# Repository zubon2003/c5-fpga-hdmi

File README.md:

# c5-fpga-hdmi

[日本語の README](README.ja.md)

> **Experimental — close range only.** This has only been seen working with
> the VTX a short distance (about 1 m, on a desk) from the receiver. Range,
> weak-signal behaviour, other VTXs and other channels have not been tested.
> Treat it as a proof of concept, not as a usable FPV receiver.

Analog 5.8 GHz FPV video (FM, NTSC) received by an ESP32-C5 running
[C5VRX](https://github.com/Twotoz/C5VRX), demodulated on a Sipeed
**Tang Primer 25K** FPGA and shown in colour on an HDMI monitor at
**1280×720p, 59.94 Hz** (CEA 720p frame timing; a 4:3 picture, 960×720 with
black pillars, or stretched to 16:9). An SDRAM field store lets the HDMI
output run on a fixed pixel clock, which HDZero goggles need; with genlock
on, the output follows the input with about 1 ms of latency and no SDRAM.

The C5VRX-5 firmware already puts the radio's raw 4-bit IQ samples
(MODEM_DIAG Q4/I4) on eight GPIO pins. The FPGA taps those pins in
parallel; the ESP32-C5 firmware keeps doing the gain control, AFC and
channel selection. Official releases up to v5.0.464 work unmodified;
later ones moved two IQ pins, and [firmware/](firmware/README.md) has a
patched v5.0.523 (see [C5VRX version](#c5vrx-version)).

## Origins

- **[fpvdec / 5G8atv-rf-hackrf-decoder](https://github.com/zubon2003/5G8atv-rf-hackrf-decoder)**
  — my HackRF One software receiver for analog FPV video, which this
  project grew out of. It is itself based on
  [famicom-rf-hackrf-decoder](https://github.com/GOROman/famicom-rf-hackrf-decoder)
  by GOROman. Its NTSC decoder and its C5VRX receive-chain emulation
  (`--c5`) were the reference for the processing here; the FPGA design
  itself is newly written HDL.
- **[C5VRX](https://github.com/Twotoz/C5VRX)** by Twotoz and the C5VRX
  contributors — the ESP32-C5 FPV receiver. This project uses its
  MODEM_DIAG IQ GPIO output (lane mapping and pin order, C5VRX-5
  `main/rf.c`), follows its "C5 RF front end plus external DSP logic"
  research (C5VRX-4 `RESEARCH.md`), its sync separator uses the line
  grid idea of the C5VRX-4 sync flywheel (`SYNC_FLYWHEEL.md`), and its
  FM demodulator extends the C5VRX-5 U85Q phase tracker and kp ladder.
  See [Credits](#credits).

## Hardware

| Part | Notes |
|---|---|
| Seeed XIAO ESP32-C5 | running C5VRX-5 (see below) |
| Sipeed Tang Primer 25K + Tang Primer 25K Dock | GW5A-LV25MG121 |
| Sipeed PMOD DVI (HDMI) module | on Dock PMOD **J5** (middle) |
| Sipeed Tang SDRAM module (32 MB, 16 bit) | on the Dock's 40-pin header **J3**; field store (`src/sdram_fb.v`), needed for genlock off (power-up, HDZero) |
| HDMI monitor or capture device | 720p input |
| 9 jumper wires (8 signals + GND), short | XIAO → Dock PMOD **J4** |
| Analog 5.8 GHz VTX (NTSC) | tested on F3 (5780 MHz) |
| Optional: USB-A plug (breakout) + 3 wires | XIAO D4/D5 → Dock USB-A host port **J13**, for the Dock buttons (band / channel) and the on-screen channel; needs the modified C5 firmware below |

### C5VRX version

Tested with the official **C5VRX-5 release `c5vrx5-v5.0.332`**
(commit `24da232`), unmodified, flashed from the
[C5VRX web flasher](https://twotoz.github.io/C5VRX/) / GitHub release.
The IQ GPIO mapping below is the one in that version (also identical in
v5.0.322). Later versions may change it; check `RF_IQ_GPIO_NUMS` in
C5VRX's `main/rf.h` (`s_iq_pins` in `main/rf.c` before v5.0.482). Set the
channel on the C5 as usual (BOOT button menu or USB console) and let its
startup calibration finish.

**Official releases from `c5vrx5-v5.0.482` on do not work with this
wiring.** C5VRX PR #263 moved Q sign from D3/GPIO7 to GPIO2 (MTMS) and
I bit 0 from D10/GPIO10 to the user-LED GPIO27, which is not on a pad.
Official releases up to `c5vrx5-v5.0.464` keep the old pins (only
v5.0.332 is tested unmodified here); the modified v5.0.523 in
[firmware/](firmware/README.md) puts both bits back.

### Optional: band / channel buttons on the Dock

To step the band and channel with the Dock's buttons and see the channel
on screen, the C5 needs a modified C5VRX-5 with a UART on its two DAC LSB
pins: [firmware/](firmware/README.md) has the patches (v5.0.523, tested
2026-10-27; the older v5.0.387 one) and the build steps. It is not an
official C5VRX release; the C5's own analog video output is off in it.
Everything else here works with the official firmware up to v5.0.464.

## Wiring (XIAO ESP32-C5 → Tang Primer 25K Dock J4)

Dock PMOD J4 pin numbers as in the Dock schematic: pins 1/2 are +3V3,
pins 3/4 are GND, pins 5..12 are signals (left column even pins, right
column odd pins). Find pin 1 with a meter (+3.3 V) before wiring.

```
   XIAO ESP32-C5                         Tang Primer 25K Dock, PMOD J4
   (top side)                                  ┌─────────┐
   GND  ──────────────────────────────── 3/4  │ 2    1  │  +3V3  (do NOT connect)
   D0   (GPIO1)  ── Q bit 0 ───────────── 5   │ 4    3  │  GND
   D1   (GPIO0)  ── Q bit 1 ───────────── 6   │ 6    5  │
   D2   (GPIO25) ── Q bit 2 ───────────── 7   │ 8    7  │
   D3   (GPIO7)  ── Q sign  ───────────── 8   │ 10   9  │
   D10  (GPIO10) ── I bit 0 ───────────── 9   │ 12  11  │
   (back side JTAG pads)                       └─────────┘
   MTDO (GPIO5)  ── I bit 1 ───────────── 10
   MTDI (GPIO3)  ── I bit 2 ───────────── 11
   MTCK (GPIO4)  ── I sign  ───────────── 12
   MTMS (GPIO2)  ── do NOT connect (driven by official C5VRX-5 firmware)
```

| J4 pin | FPGA ball | `iq[n]` | Signal | XIAO pin | ESP32-C5 GPIO |
|---|---|---|---|---|---|
| 1, 2 | +3V3 | – | not connected | – | – |
| 3 or 4 | GND | – | ground | GND | – |
| 5 | C11 | 0 | Q bit 0 | D0 | 1 |
| 6 | C10 | 1 | Q bit 1 | D1 | 0 |
| 7 | B11 | 2 | Q bit 2 | D2 | 25 |
| 8 | B10 | 3 | Q sign | D3 | 7 |
| 9 | D11 | 4 | I bit 0 | D10 | 10 |
| 10 | D10 | 5 | I bit 1 | MTDO (back pad) | 5 |
| 11 | G11 | 6 | I bit 2 | MTDI (back pad) | 3 |
| 12 | G10 | 7 | I sign | MTCK (back pad) | 4 |

- Do not connect the two 3.3 V supplies together; both boards are powered
  over their own USB. A common ground is required.
- Keep the wires short (under ~10 cm): the IQ bits change at 80 MHz.
- The three I bits on the XIAO's back-side JTAG pads need soldering.
- The PMOD DVI goes on **J5** (the middle PMOD; J6 until 2026-11-01).

The SDRAM module plugs into the Dock's 40-pin header J3 (pins as in
Sipeed's TangPrimer-25K-example `nestang-25k`). With genlock off (the
power-up setting, needed for HDZero goggles) every picture goes through
it. With genlock on (`g`) the SDRAM is bypassed, so the board can also be
used without the module: the picture appears after `g` is pressed.

Optional receiver link (modified C5 firmware only), through the Dock's
USB-A host port **J13** (a USB-A plug breakout; the port's D+ / D- go to
FPGA balls L6 / K6 through 0 Ω, with 15 kΩ to GND on both; the link is a
plain 115200 baud UART on those wires, not USB):

| USB-A pin | FPGA ball | Signal | XIAO pin | ESP32-C5 GPIO |
|---|---|---|---|---|
| 2 (D−) | K6 | C5 TX → FPGA RX | D4 | 23 |
| 3 (D+) | L6 | FPGA TX → C5 RX | D5 | 24 |
| 4 (GND) | – | ground | GND | – |
| 1 (VBUS) | – | Dock +5 V | not connected | – |

Leave VBUS unconnected while the XIAO is powered from its own USB (its
5V pin is that USB's VBUS). Remove the DAC resistors from D4/D5 if the
XIAO had the resistor DAC. Tested 2026-11-01: the channel reports arrive
(`E1 5705`); the first build had D+ / D− the other way round and got
nothing.

## Programming

Prebuilt bitstreams are attached to the
[GitHub releases](../../releases) (`c5_fpga_hdmi.fs` for the Gowin
Programmer, `c5_fpga_hdmi.bin` for other loaders). Releases up to v0.2.0
are the earlier design: no SDRAM, PMOD DVI on J6, receiver link on J5.

With the Gowin Programmer (Education edition, no licence needed), device
**GW5A-25A / GW5A-LV25MG121NC1/I0**:

```powershell
# SRAM (lost at power-off)
programmer_cli.exe --device GW5A-25A --run 2  --fsFile c5_fpga_hdmi.fs
# external flash (boots at power-on, ~3 minutes)
programmer_cli.exe --device GW5A-25A --run 54 --fsFile c5_fpga_hdmi.fs
```

If the Programmer reports a different ID, your board may be GW5A-25B:
change `set_device` in `scripts/build.tcl` and rebuild.

### Building

Gowin EDA Education 1.9.11.03 (batch mode):

```powershell
powershell -ExecutionPolicy Bypass -File scripts\build.ps1
# output: impl\pnr\c5_fpga_hdmi.fs
```

## Use

Power the XIAO (C5VRX-5 on the VTX channel) and the Dock, plug in HDMI.
The HDMI output is always 1280×720 at 59.94 Hz (59.945); with a VTX on, the picture
appears within a second, without one the picture area shows noise. The
small square at the top right of the picture is green while horizontal
sync is found, red otherwise.

Latency: with genlock off (power-up), the HDMI output runs on its own
clock and shows fields from the SDRAM field store. The added delay is
between about 0.5 ms and one field (16.7 ms), about 8 ms on average; it
drifts slowly as the output and the input clocks differ, and steps back
by one field every few minutes (one field is dropped or shown twice).
The genlock modes (`g`) lock the output to the input and bypass the SDRAM:
the display reads the lines straight from a 24-line ring, about 0.2 ms
behind the input at the top of the picture and about 1 ms at the bottom
(computed, not measured). HDZero goggles cannot follow the timing changes
genlock makes.

With the receiver link: the Dock key on H11 steps the band, the key on
H10 the channel (R, A, B, E, F, L; 1..8). The new channel name (e.g. `F3`)
appears at the top right for 3 seconds, and once at power-up.

The Dock's USB debugger has a UART (the second COM port, 1 Mbaud). Single
characters change settings at run time. Except for `P` / `W`, they are saved
in the configuration flash 2 s after the last change and come back at
power-up (`src/cfg_flash.v`, last 4 KB sector, 0x7FF000; the `R` reply's
last byte is the save status). Writing a new bitstream keeps them; the
values marked power-up below apply when nothing has been saved:

| Key | Action |
|---|---|
| `P` / `W` | picture (power-up, not saved) / waveform monitor of one demodulated line |
| `u` / `d` | first active line −/+ 1 |
| `h` / `l` | picture start −/+ 0.2 µs |
| `f` | field offset direction (interlace) |
| `c` | colour on/off |
| `v` | V sign (hue) |
| `a` / `z` | colour saturation +/− 0.25× |
| `[` / `]` | hue −/+ 11.25° |
| `m` | FM demodulator mode: 0 adjacent, 1 PLL fast, 2 PLL, 3 PLL slow (power-up) |
| `A` | picture 4:3 (960×720 with black pillars, power-up) / stretched to 16:9 |
| `g` | output genlock, in turn: off (power-up; fixed 74.18 MHz pixel clock, SDRAM field store) → porch lines → pixel clock (PLL phase steps) → off. Both genlock modes bypass the SDRAM (low latency, no module needed) |
| `K` | SDRAM read timing test (result in `T` word 13) |
| `k` | invert the SDRAM clock, then run the test |
| `T` | status packet (sync, levels, colour lock, receiver channel, SDRAM status, pixel clock meter) |
| `R` | read back the settings above (`IQLR`, 8 bytes; layout in `src/top.v`, `settings`) |
| `C` `S` `B` `G` | logic-analyser captures (raw IQ, symbols, FM output, chroma) |

`scripts/viewer.py` is the PC test app: it shows the HDMI output through
a UVC capture device and controls the FPGA over the UART.

- **Picture**: scales with the window; F11 (or View > Fullscreen) for full
  screen, Esc to leave.
- **Control panel**: every setting above as buttons (display mode, 4:3 /
  16:9, genlock mode, FM demodulator, colour, hue, saturation, picture
  position, SDRAM test, snapshot, recording, logic-analyser captures).
  The panel shows the FPGA's own settings, read back with `R` when the
  UART opens, after every key and once a second (with an older bitstream
  without `R` it tracks what it sent).
- **Live status**: the `T` packet once a second (sync, fields, levels,
  colour lock, receiver channel, pixel clock, SDRAM test result).
- **Device** menu: the capture device (default "C8 USB3.0 Video" if
  present, else the first; `--device`, `--list-devices`).
- **Port** menu: the UART (Auto = the Dock debugger's second COM port,
  found by its FTDI serial number; `--port`).
- The capture and the UART reconnect by themselves when the board or the
  capture device is unplugged and comes back.
- Keyboard: the keys above, plus `s` snapshot, `r` record, `q` quit.

Double-click `viewer.bat` in the repository root to start it (it checks
the requirements first and passes any arguments on), or:

```powershell
py -3 scripts\viewer.py
py -3 scripts\viewer.py --device "C8 USB3.0 Video" --port COM4
```

Requirements: Python 3 with numpy, pyserial and Pillow, ffmpeg on the PATH.
`scripts/iqla.py`, `demod.py`, `fm_model.py` and `resampler_model.py` are
the host tools and bit-level models used to verify each stage on the board.

## How it works

```
XIAO ESP32-C5 (C5VRX-5; official, or patched for the link): RF, ADC, gain, AFC
  │ MODEM_DIAG Q4/I4 on 8 GPIOs, ~80 MHz, no clock
  ▼
Tang Primer 25K
  IDES8 input        675 MS/s, 8.4 samples per IQ symbol
  iq_resampler       phase-tracking resampler (byte-wide Alexander detector)
                     → one IQ byte per symbol, ~80 MS/s (C5/Dock crystal
                     offset ~30 ppm tracked)
  fm_demod           amplitude-gated PLL (or adjacent difference), 22-tap boxcar
  video_in           sync separator (hysteresis, pulse widths, flywheel),
                     field / parity, black and white levels from porch and
                     sync depth, 640 pixels per line into an 8-line ring
  sdram_fb           field store in the SDRAM module: 4 field buffers;
                     input ring → SDRAM → 8-line output ring, so the
                     output does not have to follow the input (genlock
                     off); with genlock on, video_in writes the output
                     ring directly as a 24-line ring (SDRAM bypass)
  chroma             3.58 MHz NCO frequency-locked to the burst, burst
                     reference averaged over lines (hue + ACC), 1.6 µs
                     chroma low-pass, two-line chroma average
  display            240 → 720 lines with vertical interpolation (field 2
                     placed 1.5 rows lower), BT.601 RGB
  video_timing       CEA 1280×720p timing, 1650 × 750 at 74.1818 MHz
                     (59.945 Hz; two PLLs in a row), free-running by default; the
                     optional genlock moves the pixel clock (PI loop
                     driving dynamic phase steps of the second PLL) or the
                     porch line lengths
  TMDS / OSER10      → PMOD DVI (J5)
```

Notes from bring-up:

- The C5's GPIO IQ updates at 80 MHz (C5VRX itself captures it at 40 MS/s).
- A frame length that changes from frame to frame (an earlier version
  repeated the last line to wait for the input) worked on a capture card
  but not on an HDMI monitor; changing the length of picture lines sheared
  the picture on the capture card. Changing only the vertical front porch
  lines suited monitors and the capture card, but HDZero goggles (HDMI in)
  showed white and re-synced on every change, even BASE ± 1 for whole
  frames. Moving the pixel clock instead (1/8-VCO-period PLL phase steps,
  112.3 ps now; this needs an integer output divider, with the fractional
  3.625 used before the phase wrapped after three VCO periods and the
  steps did not change the frequency) also turned the goggles white. So
  the output now runs on a fixed clock and the SDRAM field store takes up
  the difference (genlock off at power-up).
- HDZero goggles from firmware 9.6.0-rc1 show black for a non-standard
  1631 × 750 frame at 73.33 MHz (the earlier timing), hence the standard
  1650 × 750 frame (at 74.1818 MHz, 81 ppm above the CEA 74.1758 MHz). A
  fractional PLL multiplier gave no picture at all, so two PLLs with integer
  multipliers run in a row (`src/pll.v`).
- Sharp horizontal edges (OSD text) still move by about a line between
  fields: each field is shown on its own (bob). The field store keeps the
  previous fields, but combining two fields (weave) is not done yet.
- After reprogramming, the capture card used during development sometimes
  stayed black until the display mode was switched once (`W`, then `P`).

Resources: about 5,000 LUTs (7,900 logic cells with ALUs), 41 of 56 BSRAM,
72 % of the DSP blocks, 2 of 6 PLLs.

A detailed development log (Japanese) is in
[docs/DEVLOG.ja.md](docs/DEVLOG.ja.md).

## License

GPL-3.0-only — see [LICENSE](LICENSE).

## Credits

This project incorporates/adapts the ESP32-C5 MODEM_DIAG IQ GPIO routing
(Q4/I4 lane mapping and pin order, C5VRX-5 `main/rf.c`) and the
"C5 RF front end plus external DSP logic" architecture research
(C5VRX-4 `legacy/c5vrx4/RESEARCH.md`), and the idea of a PLL line grid
that only accepts sync pulses near its prediction (C5VRX-4 sync flywheel,
`legacy/c5vrx4/SYNC_FLYWHEEL.md`; reimplemented here as the line PLL in
`src/video_in.v`, which times lines and does not rebuild sync pulses), and
the phase-tracker FM demodulator with selectable loop gain (C5VRX-5 U85Q
tracker and kp ladder, `main/u85q.bsasm`, `main/kp_ladder.h` and
`research/README.md`; extended here in `src/fm_demod.v` with a
second-order loop, an amplitude-gated correction and seamless mode
switching, with the signal and channel model of the C5VRX-5 range
simulator `research/sim.py` followed in `research/demod_sim.py`) from
[C5VRX], and `firmware/c5vrx5-v5.0.523-fpga-link.patch` and
`firmware/c5vrx5-v5.0.387-fpga-link.patch` modify C5VRX-5 v5.0.523
(commit `96995500`; `main/console.c`, `main/main.c`, `main/receiver.h`,
`main/rf.h`, `main/transport.c`, `main/CMakeLists.txt`) and v5.0.387
(commit `2f1a1252`; `main/console.c`, `main/transport.c`,
`main/CMakeLists.txt`) for the optional receiver link, from
[C5VRX](https://github.com/Twotoz/C5VRX) by Twotoz and the C5VRX
contributors. Visit the [official C5VRX website](https://twotoz.github.io/C5VRX/)
for the original project and its Discord invite. See the source and
license notices for the applicable terms (C5VRX is GPL-3.0-only); this
derivative is not an official C5VRX release.

- [fpvdec / 5G8atv-rf-hackrf-decoder](https://github.com/zubon2003/5G8atv-rf-hackrf-decoder)
  (GPL-3.0-only), based on GOROman's
  [famicom-rf-hackrf-decoder](https://github.com/GOROman/famicom-rf-hackrf-decoder) (MIT).
- Tang Primer 25K Dock PMOD / HDMI / SDRAM pin locations and PLL settings
  follow Sipeed's [TangPrimer-25K-example](https://github.com/sipeed/TangPrimer-25K-example)
  (`hdmi/svo` and `nestang-25k`, commit 27c1737) and the Dock schematic; the
  HDL here is newly written.

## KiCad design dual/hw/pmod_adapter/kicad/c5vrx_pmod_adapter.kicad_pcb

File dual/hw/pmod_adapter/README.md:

# C5VRX Pmod アダプタ rev A（XIAO ESP32-C5 → Tang Primer 25K Dock Pmod）

XIAO ESP32-C5（C5VRX ファーム）1台を Dock の Pmod 1口につなぐ基板。**同じ基板を2枚作り**、XIAO-A を Pmod J4（右）、XIAO-B を J5（中央）に差す。HDMI Pmod は J6（左）。

- 大きさ 19.0 × 34.5 mm、2層、1.6 mm 厚
- 配線 0.25 mm／クリアランス 0.18 mm／ビア 0.6/0.3 mm、両面ベタ GND。どの基板メーカーの標準仕様でも作れる
- DRC: エラー 0、未接続 0（`kicad/drc.rpt`）。残る警告は J1 のシルクを Fab 層へ移したことによる「ライブラリと不一致」の1件だけで、意図したもの
- 回路図: `fab/c5vrx_pmod_adapter_schematic.pdf`、外観: `images/pcb_top.png` と `images/pcb_bottom.png`

## 差す向き

Sipeed 純正 Pmod モジュールと同じく、**部品面を上にして**差す。基板の J1 側が Dock、USB-C 側が外を向く。

J1 の並び（Dock の外からのぞいた向き、左→右）:

| 段 | 左 → 右 | Pmod 番号 |
|---|---|---|
| 上段 | 3V3, GND, OPT_CLK, CVBS2, CVBS1, CVBS0 | 6, 5, 4, 3, 2, 1 |
| 下段 | 3V3, GND, (空き), CVBS5, CVBS4, CVBS3 | 12, 11, 10, 9, 8, 7 |

KiCad 上の J1 のピン番号（1〜12、奇数が上段）は Pmod 標準の番号とは別物なので注意。FPGA ボールとの対応は `../../design/interface.md` §2〜§3。

## 回路

- **XIAO の D4〜D9 → 33 Ω（R1〜R6）→ Pmod**。ダンピング抵抗で、40 MHz 出力のリンギングを抑える。
- XIAO の D0〜D3、D10 は C5VRX が内部の RF IQ ループバックに使うので**どこにもつないでいない**。
- **XIAO は 1×7 のピンソケット2本に差す**（基板に直接はんだ付けしない）。R1〜R6、C2、C3、JP1、D1 は XIAO の下にある。

## 電源

- **J2（5V, G）**: Dock 裏のデバッガ部の「5V」パッドから線を引いてつなぐ。D1（B5819W）を通って XIAO の 5V ピンへ入る。
  - XIAO に USB をつないだときに Dock 側へ逆流するのを D1 が防ぐ。XIAO が受ける電圧は約 4.6 V。
  - Dock の 5V は USB-C 給電で、ポリスイッチ（2 A）経由。合計は 0.6〜0.8 A の見込みなので、5V/2A 電源を使う。
- **JP1（ソルダージャンパ、初期状態は開放）**: はんだで閉じると XIAO の 3V3 が Pmod の 3V3 とつながる。
  - J2 を使わないときだけ閉じる。
  - 閉じている間は XIAO に USB を挿さないこと（XIAO と Dock の 3.3V 同士がぶつかる）。
- GND は Pmod の GND ピン（2本）と J2 の G の両方で Dock と共通。

## OPT_CLK（任意）

- **TP1（CLK）** は Pmod の IO4 につながっている。J4 では C11（GCLKT_13）、J5 では L5（GCLKT_3）。
- 使う場合は XIAO 裏の MTMS パッド（GPIO2）から細線で TP1 へ配線し、C5VRX の `main/video.c` の `create_tx_unit()` で `clk_out_gpio_num = 2` にする。
- 使わなければ FPGA は 160 MHz の非同期オーバーサンプリングで受ける（設計メモ §4）。

## アナログ映像出力（任意、初期状態は未実装）

- 裏面の R10〜R16 と C4 は C5VRX 本来の抵抗 DAC（参考定数）。
- 実装すると J3（VID, G）からアナログ CVBS が出るので、FPGA と並行してモニタで確認できる。
- 通常は実装しない（BOM で DNP）。

## 製造データ

| ファイル | 内容 |
|---|---|
| `fab/c5vrx_pmod_adapter_gerber.zip` | ガーバー＋ドリル（そのまま基板メーカーへ） |
| `fab/c5vrx_pmod_adapter_bom.csv` | 部品表（DNP 含む。XIAO 用 1×7 ピンソケット ×2 も記載） |
| `fab/c5vrx_pmod_adapter_pos.csv` | 実装位置（表面部品、DNP 除く、原点は基板左下） |
| `kicad/` | KiCad 7 プロジェクト一式（独自ライブラリ c5vrx 同梱） |
| `scripts/` | 生成スクリプト。`design.py` が部品・ネット・配置の元データで、`run.sh` で回路図生成から配線、DRC まで再実行できる（自動配線は Freerouting 2.1） |

## 確認してほしいこと

- **Pmod 間隔**: 写真から約 22 mm と見積もった値で、まだ実測していない。
  - 基板幅は 19 mm なので、隣の Pmod との間に約 3 mm の余裕がある見込み。
  - XIAO の USB-C 側は基板の外側にあるため、隣り合わない。
  - 発注前に、J4 と J5 の中心間をノギスで測ってほしい。
- **J1 の高さ**: J1 は普通の 2×6 L字ピンヘッダ。Dock の Pmod ソケットの高さと合うかを、手元の HDMI Pmod と並べて確認してほしい。

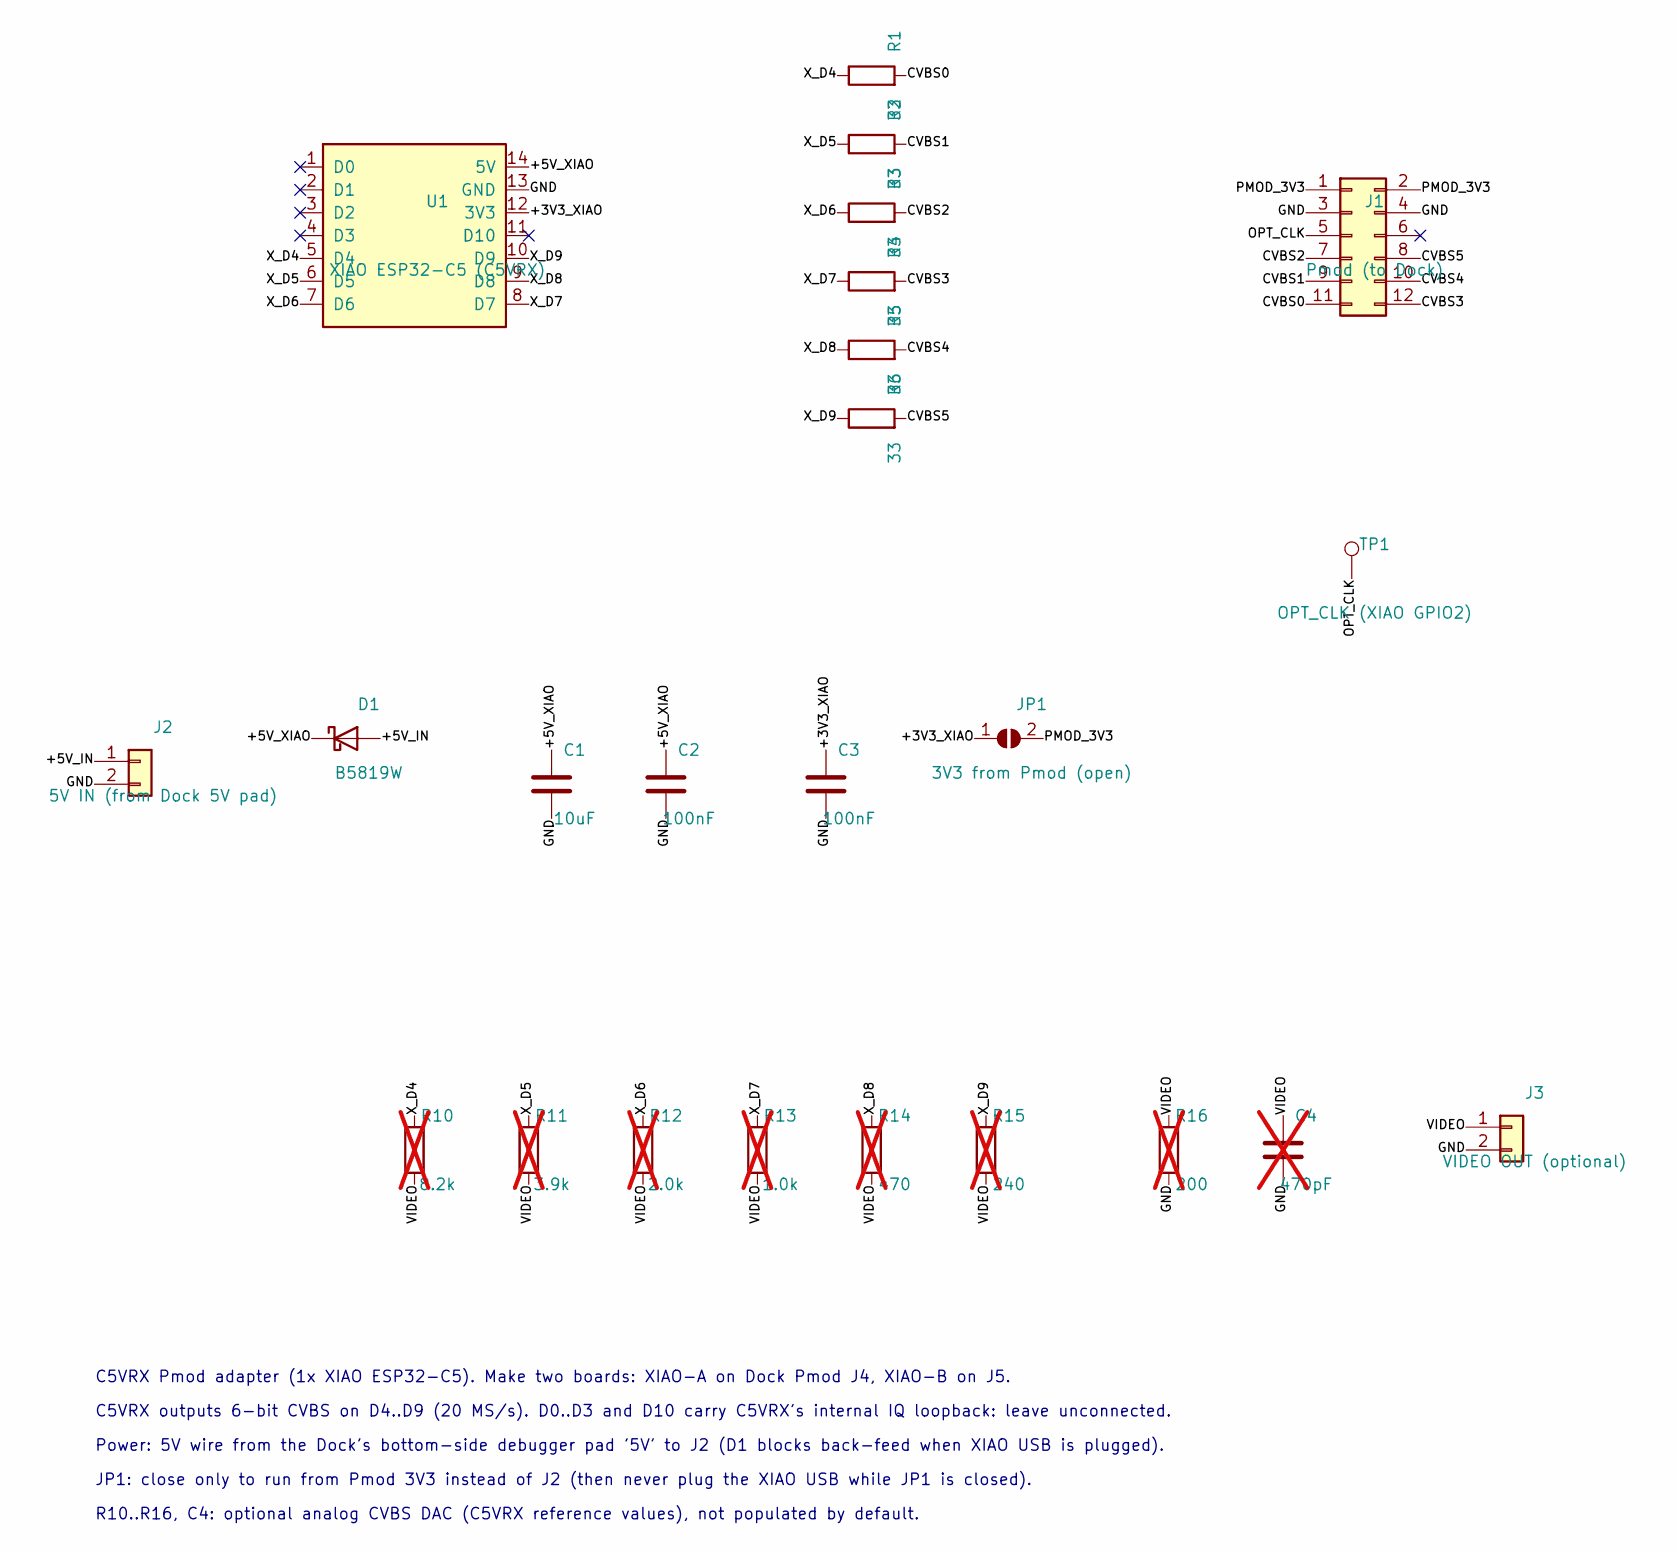
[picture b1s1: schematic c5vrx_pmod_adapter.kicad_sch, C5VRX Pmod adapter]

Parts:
C1: 10uF; C_0805_2012Metric
C2, C3: 100nF; C_0603_1608Metric
C4: 470pF; C_0603_1608Metric; not fitted
D1: B5819W; D_SOD-123
J1: Pmod (to Dock); PinHeader_2x06_P2.54mm_Horizontal
J2: 5V IN (from Dock 5V pad); PinHeader_1x02_P2.54mm_Vertical
J3: VIDEO OUT (optional); PinHeader_1x02_P2.54mm_Vertical
JP1: 3V3 from Pmod (open); SolderJumper-2_P1.3mm_Open_RoundedPad1.0x1.5mm
R1, R2, R3, R4, R5, R6: 33; R_0603_1608Metric
R10: 8.2k; R_0603_1608Metric; not fitted
R11: 3.9k; R_0603_1608Metric; not fitted
R12: 2.0k; R_0603_1608Metric; not fitted
R13: 1.0k; R_0603_1608Metric; not fitted
R14: 470; R_0603_1608Metric; not fitted
R15: 240; R_0603_1608Metric; not fitted
R16: 200; R_0603_1608Metric; not fitted
TP1: OPT_CLK (XIAO GPIO2); TestPoint_THTPad_D1.5mm_Drill0.7mm
U1: XIAO ESP32-C5 (C5VRX); XIAO_THT_Socket

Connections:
+3V3_XIAO: C3.1, JP1.1 (A), U1.12 (3V3)
+5V_IN: D1.2 (A), J2.1
+5V_XIAO: C1.1, C2.1, D1.1 (K), U1.14 (5V)
CVBS0: J1.11, R1.2
CVBS1: J1.9, R2.2
CVBS2: J1.7, R3.2
CVBS3: J1.12, R4.2
CVBS4: J1.10, R5.2
CVBS5: J1.8, R6.2
GND: C1.2, C2.2, C3.2, C4.2, J1.3, J1.4, J2.2, J3.2, R16.2, U1.13 (GND)
OPT_CLK: J1.5, TP1.1
PMOD_3V3: J1.1, J1.2, JP1.2 (B)
VIDEO: C4.1, J3.1, R10.2, R11.2, R12.2, R13.2, R14.2, R15.2, R16.1
X_D4: R1.1, R10.1, U1.5 (D4)
X_D5: R2.1, R11.1, U1.6 (D5)
X_D6: R3.1, R12.1, U1.7 (D6)
X_D7: R4.1, R13.1, U1.8 (D7)
X_D8: R5.1, R14.1, U1.9 (D8)
X_D9: R6.1, R15.1, U1.10 (D9)

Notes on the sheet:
C5VRX Pmod adapter (1x XIAO ESP32-C5). Make two boards: XIAO-A on Dock Pmod J4, XIAO-B on J5.
C5VRX outputs 6-bit CVBS on D4..D9 (20 MS/s). D0..D3 and D10 carry C5VRX's internal IQ loopback: leave unconnected.
Power: 5V wire from the Dock's bottom-side debugger pad '5V' to J2 (D1 blocks back-feed when XIAO USB is plugged).
JP1: close only to run from Pmod 3V3 instead of J2 (then never plug the XIAO USB while JP1 is closed).
R10..R16, C4: optional analog CVBS DAC (C5VRX reference values), not populated by default.

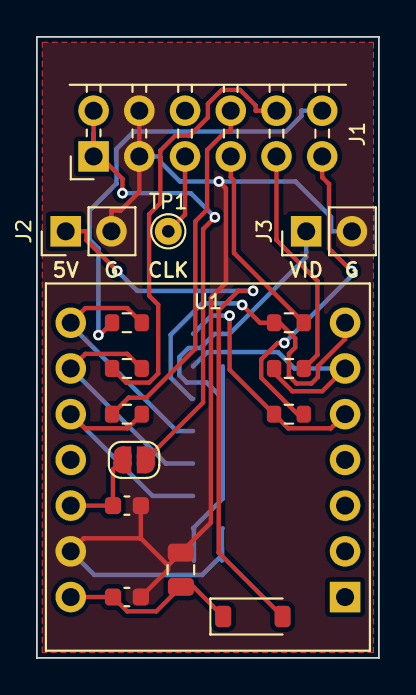
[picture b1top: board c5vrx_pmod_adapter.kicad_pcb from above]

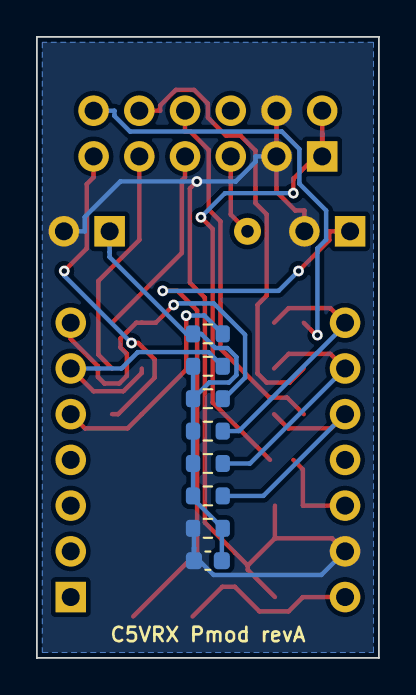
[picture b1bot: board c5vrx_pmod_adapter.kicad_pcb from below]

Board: 2 copper layers, 19.0 x 34.5 mm, 24 parts (8 on the bottom side), 19 nets.

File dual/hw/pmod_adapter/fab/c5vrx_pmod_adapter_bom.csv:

Refs,Qty,Value,Footprint,Populate,Note
U1,1,XIAO ESP32-C5 (C5VRX),XIAO_THT_Socket,yes,Seeed XIAO ESP32-C5 on 2x 1x7 female sockets
J1,1,Pmod (to Dock),PinHeader_2x06_P2.54mm_Horizontal,yes,2x6 right-angle male header 2.54mm
R1 R2 R3 R4 R5 R6,6,33,R_0603_1608Metric,yes,
D1,1,B5819W,D_SOD-123,yes,Schottky 40V 1A SOD-123
C1,1,10uF,C_0805_2012Metric,yes,10V X5R
C2 C3,2,100nF,C_0603_1608Metric,yes,
JP1,1,3V3 from Pmod (open),SolderJumper-2_P1.3mm_Open_RoundedPad1.0x1.5mm,yes,Close only when not using 5V input
J2,1,5V IN (from Dock 5V pad),PinHeader_1x02_P2.54mm_Vertical,yes,wire pads
TP1,1,OPT_CLK (XIAO GPIO2),TestPoint_THTPad_D1.5mm_Drill0.7mm,yes,wire from XIAO back pad MTMS
R10,1,8.2k,R_0603_1608Metric,DNP,DNP
R11,1,3.9k,R_0603_1608Metric,DNP,DNP
R12,1,2.0k,R_0603_1608Metric,DNP,DNP
R13,1,1.0k,R_0603_1608Metric,DNP,DNP
R14,1,470,R_0603_1608Metric,DNP,DNP
R15,1,240,R_0603_1608Metric,DNP,DNP
R16,1,200,R_0603_1608Metric,DNP,DNP
C4,1,470pF,C_0603_1608Metric,DNP,DNP
J3,1,VIDEO OUT (optional),PinHeader_1x02_P2.54mm_Vertical,yes,"wire pads, DAC parts DNP"
(U1 socket),2,1x7 female header 2.54mm,-,yes,XIAO socket strips

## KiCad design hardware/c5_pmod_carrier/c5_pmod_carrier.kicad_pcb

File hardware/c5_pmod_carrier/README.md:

# XIAO ESP32-C5 PMOD carrier

A 20 x 36 mm two-layer board that plugs a XIAO ESP32-C5 (C5VRX-5) into a
Tang Primer 25K Dock PMOD port (J4 or J6; J5 holds the PMOD DVI). All eight IQ lines go through
the PMOD plug; UART, 5 V and ground are wire pads on the bottom edge. The
same board is used for both receivers of the diversity setup.

v3: the XIAO is turned 90 degrees clockwise (top view): antenna end
towards the PMOD plug, USB-C pointing away from the Dock. The XIAO
(17.8 mm wide) now sits inside the 20 mm board width. The board is 20 mm
wide (v1 was 33 mm) so that it clears the parts next to the PMOD port.
All right-angle track corners are cut to two 45 degree bends. The PMOD
pin order changed again with the rotation (see Signals).

Not built or tested yet.

## Files

| File | |
|---|---|
| `gen_board.py` | generates the board (KiCad 8 Python); edit this, not the PCB |
| `c5_pmod_carrier.kicad_pcb` | the board (KiCad 8) |
| `c5_pmod_carrier_gerber.zip`, `gerber/` | Gerber + Excellon for the board house |
| `panelize.py` | makes the V-cut panel from the single board (run after `gen_board.py`) |
| `c5_pmod_carrier_panel.kicad_pcb`, `c5_pmod_carrier_panel_gerber.zip`, `gerber_panel/` | the panel and its Gerbers (only the zip is in git; `panelize.py` makes the rest) |
| `LOGO_*.kicad_mod` | logos; `gen_board.py` scales them and puts them on the back silkscreen (ZUBON TECH. 18 mm wide along the bottom edge, Tinywhoop 11.5 mm between the socket columns) |

Regenerate: `"C:/Program Files/KiCad/8.0/bin/python.exe" gen_board.py`,
then re-export the Gerbers with `kicad-cli pcb export gerbers` / `drill`.
DRC (2026-10-31, v3): 0 errors, 0 unconnected; 8 warnings that the custom
footprints are not in a library.

## Parts

| Ref | Part |
|---|---|
| J1 | 2x6 pin header, 2.54 mm, **right angle**, male, on the top side |
| J2, J3 | 1x7 female socket, 2.54 mm, vertical (the XIAO plugs in with its own male headers) |
| D1 | Schottky diode, SOD-123: ROHM RB160M-30 (30 V 1 A, Vf 0.43 V; Akizuki 101398). Any 1 A Schottky in SOD-123 fits |

## Orientation

Dock PMOD numbering (Dock schematic): 1/2 = +3V3, 3/4 = GND, 5..12
signals. Looking into the Dock socket from outside with the Dock
component side up, pins 1/2 are on the left and the odd pins are in the
upper row (checked on J4 against the existing wiring). The carrier then
plugs in level with the Dock, component side up ("THIS SIDE UP"), with
the square pad (pin 1) on the left. Plugged in upside down, the XIAO
outputs would drive the Dock's +3V3 and GND pins.

PMOD pins 1/2 (+3V3) are not connected; the XIAO runs from the 5 V pad.

## Signals

The PMOD order is chosen so that all traces are on the top layer
without crossings (the bottom layer is a solid ground plane), so it is
not the order of the earlier jumper wiring (nor of v1/v2). `top.cst` has
to follow it:

| PMOD | Signal | XIAO | J4 pin (FPGA) | J6 pin (FPGA) |
|---|---|---|---|---|
| 5 | I bit 1 | MTDO (GPIO5), wire | C11 | H5 |
| 6 | I bit 0 | D10 (GPIO10) | C10 | J5 |
| 7 | I bit 2 | MTDI (GPIO3), wire | B11 | H8 |
| 8 | I sign | MTCK (GPIO4), wire | B10 | H7 |
| 9 | Q bit 1 | D1 (GPIO0) | D11 | G7 |
| 10 | Q bit 0 | D0 (GPIO1) | D10 | G8 |
| 11 | Q sign | D3 (GPIO7) | G11 | F5 |
| 12 | Q bit 2 | D2 (GPIO25) | G10 | G5 |

So for the receiver on J4: `iq[0]` D10, `iq[1]` D11, `iq[2]` G10,
`iq[3]` G11, `iq[4]` C10, `iq[5]` C11, `iq[6]` B11, `iq[7]` B10; on J6:
G8, G7, G5, F5, J5, H5, H8, H7.

The PMOD DVI moved to the middle port J5 on 2026-11-01, so the second
receiver goes on J6. The receiver UART is on the Dock USB-A port (FPGA
L6 = D+ to the C5's RX, K6 = D- from its TX; `top.cst`), not on a PMOD.

## Wires

Bottom edge, right to left (2.54 mm apart): RX, TX, GND, 5V. D1 sits at
the bottom left, below the XIAO's 5V pin.

| Pad | To |
|---|---|
| RX (D5) | FPGA TX (both receivers on one wire) |
| TX (D4) | FPGA RX (receiver 1 only) |
| GND | Dock GND |
| 5V | Dock +5 V: USB-A VBUS (pin 1), or J7 pin 4 |
| MTDO, MTDI, MTCK holes | the XIAO's bottom-side pads of the same name; the wire goes down through the hole and is soldered on the back |

D1 keeps the XIAO's own USB VBUS out of the Dock's 5 V, so the XIAO's
USB-C can stay plugged into a PC (the XIAO 5V pin is its VBUS).

XIAO geometry (pins, 15.24 mm rows, bottom pads) is taken from Seeed's
"Seeed Studio XIAO ESP32C5 V1.1" KiCad project (2025-12-25).

## Panel

`panelize.py` puts 4 x 2 boards side by side with no gap and adds a 5 mm
rail (no copper) on the top and bottom edge: 80 x 82 mm, 8 boards. All
inner lines are V-cuts, straight across the panel, including the line
between each rail and the boards. They are in Edge.Cuts together with the
panel outline, and again in Cmts.User (`User_Comments.gbr` in the zip)
with "V-CUT" labels. Copper stays 0.5 mm from every board edge.

When ordering, choose the board house's "panel by customer" option with
V-cut, give the panel size (80 x 82 mm) and note that the inner outline
lines are the V-cuts. The panel DRC reports the copies as unconnected
because they share net names; DRC is checked on the single board.

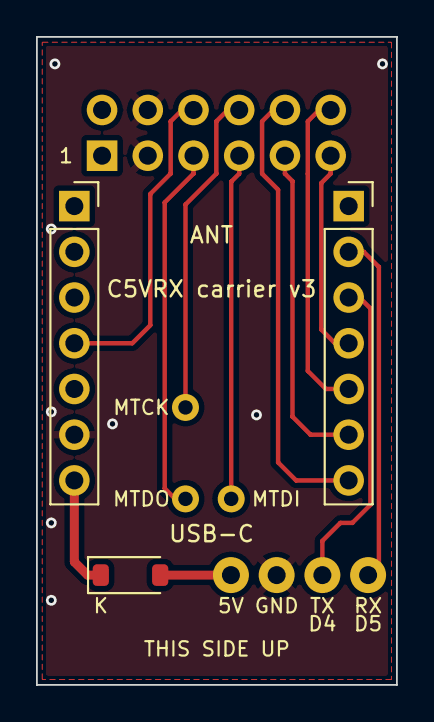
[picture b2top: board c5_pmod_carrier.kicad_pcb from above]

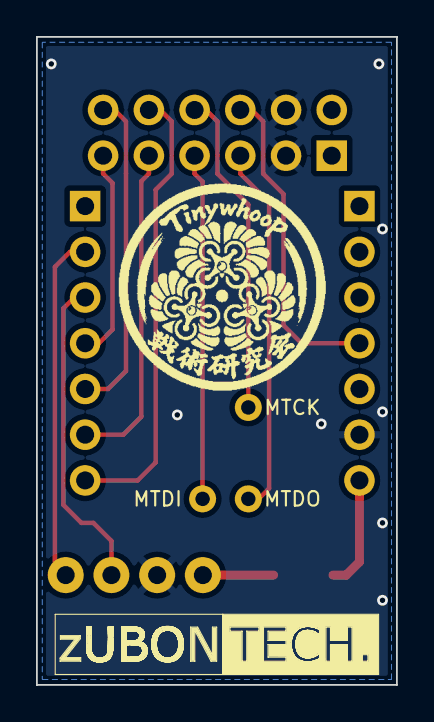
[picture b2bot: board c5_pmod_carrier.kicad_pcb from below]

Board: 2 copper layers, 20.0 x 36.0 mm, 13 parts (2 on the bottom side), 13 nets.

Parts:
D1: RB160M-30; D_SOD-123
J1: PMOD 2x6 R/A male; PMOD_2x06_RightAngle_Male
J2, J3: PinSocket_1x07_P2.54mm_Vertical
J4, J5, J6, J7: WirePad
LOGO1: LOGO_ZUBONTECH_RX5808v3_x2
LOGO2: LOGO; LOGO_TinywhoopLab_15mm
TP1, TP2, TP3: JTAGWireHole

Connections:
+5V_IN: D1.2, J7.1
C5_RX: J2.2, J4.1
C5_TX: J2.3, J5.1
GND: J1.3, J1.4, J3.6, J6.1
I0: J1.6, J3.4
I1: J1.5, TP1.1
I2: J1.7, TP2.1
IS: J1.8, TP3.1
Q0: J1.10, J2.7
Q1: J1.9, J2.6
Q2: J1.12, J2.5
QS: J1.11, J2.4
VBUS: D1.1, J3.7

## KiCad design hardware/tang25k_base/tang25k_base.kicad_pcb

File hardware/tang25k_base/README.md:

# Tang Primer 25K core base board

A 100 x 50 mm four-layer board that replaces the Tang Primer 25K Dock for
this project: the 25K core module, one SDRAM, USB-C JTAG/UART, one HDMI
output, both XIAO ESP32-C5 receivers on sockets, and six buttons.

Not built or tested yet.

## Files

| File | |
|---|---|
| `gen_base.py` | places the parts and sets the nets (KiCad 8 Python); edit this, not the PCB |
| `route.py` | runs `gen_base.py`, draws the HDMI traces, routes the rest with Freerouting 1.7, fills the planes |
| `tang25k_base.kicad_pcb`, `.kicad_pro` | the board (KiCad 8) |
| `export_jlc.py` | writes `jlcpcb/`: Gerber zip, BOM and CPL for JLCPCB assembly (LCSC numbers in the script; XIAO sockets left for hand soldering) |

Rebuild: `"C:/Program Files/KiCad/8.0/bin/python.exe" route.py 40`
(Freerouting from `%LOCALAPPDATA%\freerouting`; about 10 minutes. More
passes than about 40 sometimes never finish.)

## Layers

F.Cu and B.Cu signals, In1.Cu GND plane, In2.Cu +3V3 plane, GND pours on
both outer layers. Tracks 0.15 mm / clearance 0.127 mm, +5V and the XIAO
and HDMI 5 V nets 0.4 mm; vias 0.5 / 0.25 mm. Copper stays 0.45 mm off the
edge. All parts are on the top side.

## Core module

Two Hirose DF40C-60DS-0.4V(51) receptacles, 14.0 mm apart, placed as on
the Dock (pad geometry from Sipeed's `Tang_Primer_25K_Dock_60033_ibom.html`,
pin functions from the Dock and core schematics). The connectors need
reflow (JLCPCB assembly). The area under the module (silk corner marks)
has no parts.

The module makes its own 3.3 V (J2 46/48/50); the board feeds +5 V into
J2 52..60 and the bank supplies VCCIO0/1, VCCIO2/3, VCCIO6/7 from 3.3 V
through ferrite beads, as the Dock does. The 50 MHz oscillator (E2) and
the configuration flash are on the module.

## Parts

| Ref | Part |
|---|---|
| J1, J2 | Hirose DF40C-60DS-0.4V(51) |
| U1 | FTDI FT2232HL (LQFP-64), Y1 12 MHz (3225), U2 93LC56B EEPROM (optional) |
| U3 | Winbond W9825G6KH-6I, 32 MB SDRAM (TSOP-II 54) |
| U4 | 74HC165 (SOIC-16) |
| U6 | USBLC6-2SC6 (USB ESD) |
| J3 | USB-C, HRO TYPE-C-31-M-12 |
| J4 | HDMI type A, Amphenol 10029449-x01xLF footprint |
| J5..J8 | 1x7 female sockets for the two XIAOs |
| SW1..SW7 | XKB TS-1187A (5.1 x 5.1 mm) |
| D1, D2, D3 | ROHM RB160M-30: 5 V to each XIAO and to HDMI pin 18 |
| F1 | 1.5 A PTC (1206) |

## USB-C

FT2232HL, bus powered from the board's 3.3 V. Channel A is JTAG (MPSSE:
ADBUS0 TCK, 1 TDI, 2 TDO, 3 TMS) for openFPGALoader (`-c ft2232`) or the
Gowin programmer; channel B is a UART to the FPGA. Without the EEPROM
the chip enumerates as the stock 0403:6010.

## FPGA pins

Unchanged from `top.cst`: clock E2, SDRAM (except CS# and DQM), receiver 1
`iq[0..7]`, HDMI pairs, `link_tx` L5, `link_rx` K5, UART B3 (RX) / C3 (TX).

| Signal | Pin | Note |
|---|---|---|
| SDRAM CS#, LDQM, UDQM | - | tied to GND on the board (`sdram_fb.v` already drives DQM low) |
| SDRAM CKE | - | tied to 3.3 V |
| receiver 2 `iq2[0..7]` (Q0 Q1 Q2 QS I0 I1 I2 IS) | E11 E10 A11 A10 K11 L11 L6 K6 | |
| receiver 2 TX (`link_rx2`) | K9 | |
| 74HC165 SH/LD#, CLK, QH | H11, H10, L8 | buttons, active low, A..F = SW1..SW6 |
| user LED | L7 | high = on |
| JTAG | C1 TCK, B1 TMS, A2 TDO, A3 TDI | dedicated pins |
| DONE | D7 | LED |
| RECONFIG_N | D8 | SW7 |

The HDMI pairs keep the pins of `top.cst`, but on the board every pair's
P and N are swapped (H8, G7, F5, H5 go to the connector's minus pins) so
the traces run straight without crossing. The HDL has to invert the
serialised TMDS bits of all four channels.

Receiver wiring per XIAO: D0..D3 = Q0, Q1, Q2, Q sign; D10 = I0; D4 = TX
to the FPGA; D5 = RX from `link_tx` (both receivers); MTDO, MTDI, MTCK
(I1, I2, I sign) through wire holes under the XIAO, soldered on the back,
as on the PMOD carrier.

## Buttons

The 74HC165 loads A..F (SW1..SW6, pulled up, pressed = 0) on SH/LD# low,
then shifts on CLK; QH shows H first (tied high), then G (high), F..A.
Silk names: UP, DOWN, LEFT, RIGHT, OK, BACK.

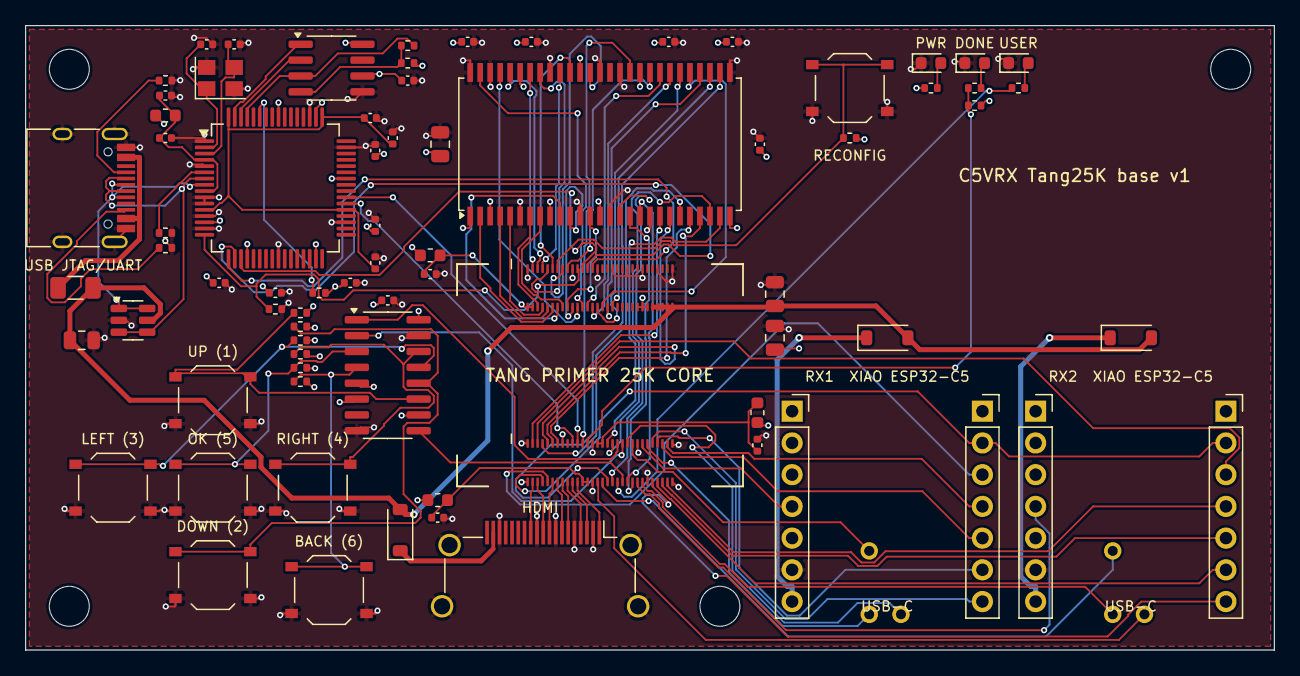
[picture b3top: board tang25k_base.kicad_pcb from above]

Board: 4 copper layers, 100.0 x 50.0 mm, 87 parts (0 on the bottom side), 107 nets.

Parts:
C1, C2: 22uF; C_0805_2012Metric
C3, C4, C5, C10, C11, C12, C13, C15, C23, C25, C26, C27, C28, C29, C30, C32, C33: 100nF; C_0402_1005Metric
C6, C14: 10uF; C_0805_2012Metric
C20, C21: 27pF; C_0402_1005Metric
C22, C24, C31: 4.7uF; C_0402_1005Metric
D1, D2, D3: RB160M-30; D_SOD-123
D10, D11, D12: green; LED_0603_1608Metric
F1: 1.5A PTC; Fuse_1206_3216Metric
FB1, FB2, FB3, FB4: 600R@100MHz; L_0603_1608Metric
H1, H2, H3, H4: M3; MountingHole_3.2mm_M3
J1, J2: DF40C-60DS-0.4V(51); Hirose_DF40C-60DS-0.4V_2x30_P0.4mm
J3: TYPE-C-31-M-12; USB_C_Receptacle_HRO_TYPE-C-31-M-12
J4: HDMI A; HDMI_A_Amphenol_10029449-x01xLF_Horizontal
J5, J6, J7, J8: 1x7 socket; PinSocket_1x07_P2.54mm_Vertical
M1: Tang Primer 25K core; Tang_Primer_25K_core_outline
R1, R2, R5: 5.1k; R_0402_1005Metric
R3: 12k 1%; R_0402_1005Metric
R4, R7, R10, R11, R12, R13, R14, R15, R16, R22: 10k; R_0402_1005Metric
R6: 2.2k; R_0402_1005Metric
R20, R21, R23: 1k; R_0402_1005Metric
SW1, SW2, SW3, SW4, SW5, SW6, SW7: TS-1187A; SW_Push_1P1T_XKB_TS-1187A
TP11, TP12, TP13, TP21, TP22, TP23: WireHole
U1: FT2232HL; LQFP-64_10x10mm_P0.5mm
U2: 93LC56B; SOIC-8_3.9x4.9mm_P1.27mm
U3: W9825G6KH-6I; TSOP-II-54_22.2x10.16mm_P0.8mm
U4: 74HC165; SOIC-16_3.9x9.9mm_P1.27mm
U6: USBLC6-2SC6; SOT-23-6
Y1: 12MHz; Crystal_SMD_3225-4Pin_3.2x2.5mm

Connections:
+3V3: C2.1, C10.1, C11.1, C12.1, C13.1, C14.1, C15.1, C27.1, C28.1, C29.1, C30.1, C31.1, C32.1, C33.1, FB1.1, FB2.1, FB3.1, FB4.1, J2.46, J2.48, J2.50, R4.2, R7.2, R10.2, R11.2, R12.2, R13.2, R14.2, R15.2, R16.2, R20.1, R22.2, U1.14, U1.20, U1.31, U1.42, U1.50, U1.56, U2.6, U2.8, U3.1, U3.3, U3.9, U3.14, U3.27, U3.37, U3.43, U3.49, U4.5, U4.6, U4.10, U4.16
+5V: C1.1, C6.1, D1.2, D2.2, D3.2, F1.2, J2.52, J2.54, J2.56, J2.58, J2.60, U6.5
BTN1: R10.1, SW1.1, U4.11
BTN2: R11.1, SW2.1, U4.12
BTN3: R12.1, SW3.1, U4.13
BTN4: R13.1, SW4.1, U4.14
BTN5: R14.1, SW5.1, U4.3
BTN6: R15.1, SW6.1, U4.4
BTN_CLK: J1.39, U4.2
BTN_LD: J1.37, U4.1
BTN_Q: J1.40, U4.9
CC1: J3.A5, R1.1
CC2: J3.B5, R2.1
DONE: J1.25, R21.1, R22.1
EECLK: U1.62, U2.2
EECS: U1.63, U2.1
EEDATA: R6.2, U1.61, U2.3
EE_DO: R6.1, R7.1, U2.4
FT_PWRSAV: R4.1, U1.59
FT_REF: R3.1, U1.6
GND: C1.2, C2.2, C3.2, C4.2, C5.2, C6.2, C10.2, C11.2, C12.2, C13.2, C14.2, C15.2, C20.2, C21.2, C22.2, C23.2, C24.2, C25.2, C26.2, C27.2, C28.2, C29.2, C30.2, C31.2, C32.2, C33.2, D10.1, D11.1, D12.1, J1.1, J1.2, J1.15, J1.27, J1.28, J1.45, J1.50, J1.59, J1.60, J2.1, J2.19, J2.29, J2.35, J2.41, J2.47, J2.53, J2.59, J3.A1, J3.A12, J3.B1, J3.B12, J3.S1, J4.2, J4.5, J4.8, J4.11, J4.17, J4.SH, J6.6, J8.6, R1.2, R2.2, R3.2, R5.2, SW1.2, SW2.2, SW3.2, SW4.2, SW5.2, SW6.2, SW7.2, U1.1, U1.5, U1.10, U1.11, U1.13, U1.15, U1.25, U1.35, U1.47, U1.51, U2.5, U3.6, U3.12, U3.15, U3.19, U3.28, U3.39, U3.41, U3.46, U3.52, U3.54, U4.8, U4.15, U6.2, Y1.2, Y1.4
HDMI_5V: D3.1, J4.18
LED_DONE: D11.2, R21.2
LED_PWR: D10.2, R20.2
LED_USER: J1.38, R23.1
LED_USER_A: D12.2, R23.2
LINK_TX: J1.8, J5.2, J7.2
R1_I0: J1.47, J6.4
R1_I1: J1.49, TP11.1
R1_I2: J1.41, TP12.1
R1_IS: J1.43, TP13.1
R1_Q0: J1.51, J5.7
R1_Q1: J1.53, J5.6
R1_Q2: J1.55, J5.5
R1_QS: J1.57, J5.4
R1_TX: J1.10, J5.3
R1_VBUS: D1.1, J6.7
R2_I0: J1.46, J8.4
R2_I1: J1.48, TP21.1
R2_I2: J1.30, TP22.1
R2_IS: J1.32, TP23.1
R2_Q0: J1.52, J7.7
R2_Q1: J1.54, J7.6
R2_Q2: J1.56, J7.5
R2_QS: J1.58, J7.4
R2_TX: J1.5, J7.3
R2_VBUS: D2.1, J8.7
RECONFIG_N: J2.13, R16.1, SW7.1
SD_A0: J1.13, U3.23
SD_A1: J1.11, U3.24
SD_A2: J1.35, U3.25
SD_A3: J1.33, U3.26
SD_A4: J1.34, U3.29
SD_A5: J2.36, U3.30
SD_A6: J2.34, U3.31
SD_A7: J2.32, U3.32
SD_A8: J2.30, U3.33
SD_A9: J2.28, U3.34
SD_A10: J1.7, U3.22
SD_A11: J2.26, U3.35
SD_A12: J2.17, U3.36
SD_BA0: J1.3, U3.20
SD_BA1: J1.9, U3.21
SD_CAS: J1.44, U3.17
SD_CLK: J1.23, U3.38
SD_DQ0: J2.12, U3.2
SD_DQ1: J2.10, U3.4
SD_DQ2: J2.8, U3.5
SD_DQ3: J2.6, U3.7
SD_DQ4: J2.16, U3.8
SD_DQ5: J2.14, U3.10
SD_DQ6: J2.20, U3.11
SD_DQ7: J2.18, U3.13
SD_DQ8: J2.15, U3.42
SD_DQ9: J2.11, U3.44
SD_DQ10: J2.7, U3.45
SD_DQ11: J2.9, U3.47
SD_DQ12: J2.3, U3.48
SD_DQ13: J2.5, U3.50
SD_DQ14: J2.22, U3.51
SD_DQ15: J2.24, U3.53
SD_RAS: J1.42, U3.18
SD_WE: J1.36, U3.16
TCK: J2.21, R5.1, U1.16
TDI: J2.27, U1.17
TDO: J2.25, U1.18
TMDS0_N: J1.12, J4.9
TMDS0_P: J1.14, J4.7
TMDS1_N: J1.16, J4.6
TMDS1_P: J1.18, J4.4
TMDS2_N: J1.20, J4.3
TMDS2_P: J1.22, J4.1
TMDSC_N: J1.4, J4.12
TMDSC_P: J1.6, J4.10
TMS: J2.23, U1.19
UART_RXD: J1.19, U1.38
UART_TXD: J1.21, U1.39
USB_DM: J3.A7, J3.B7, U1.7, U6.3, U6.4
USB_DP: J3.A6, J3.B6, U1.8, U6.1, U6.6
V1V8: C24.1, C25.1, C26.1, U1.12, U1.37, U1.49, U1.64
VBUS: F1.1, J3.A4, J3.A9, J3.B4, J3.B9
VCCIO01: C3.1, FB1.2, J1.24, J1.26
VCCIO23: C5.1, FB3.2, J2.2, J2.4
VCCIO67: C4.1, FB2.2, J1.29, J1.31
VPHY: C22.1, C23.1, FB4.2, U1.4, U1.9
XI: C20.1, U1.2, Y1.1
XO: C21.1, U1.3, Y1.3

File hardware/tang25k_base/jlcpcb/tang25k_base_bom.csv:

Comment,Designator,Footprint,LCSC
22uF,"C1,C2",C_0805_2012Metric,C45783
100nF,"C3,C4,C5,C10,C11,C12,C13,C15,C23,C25,C26,C27,C28,C29,C30,C32,C33",C_0402_1005Metric,C1525
10uF,"C6,C14",C_0805_2012Metric,C15850
27pF,"C20,C21",C_0402_1005Metric,C1557
4.7uF,"C22,C24,C31",C_0402_1005Metric,C23733
RB160M-30,"D1,D2,D3",D_SOD-123,C323857
green,"D10,D11,D12",LED_0603_1608Metric,C72043
1.5A PTC,F1,Fuse_1206_3216Metric,C20802
600R@100MHz,"FB1,FB2,FB3,FB4",L_0603_1608Metric,C1015
DF40C-60DS-0.4V(51),"J1,J2",Hirose_DF40C-60DS-0.4V_2x30_P0.4mm,C597938
TYPE-C-31-M-12,J3,USB_C_Receptacle_HRO_TYPE-C-31-M-12,C165948
HDMI A,J4,HDMI_A_Amphenol_10029449-x01xLF_Horizontal,C427307
5.1k,"R1,R2,R5",R_0402_1005Metric,C25905
12k 1%,R3,R_0402_1005Metric,C25752
10k,"R4,R7,R10,R11,R12,R13,R14,R15,R16,R22",R_0402_1005Metric,C25744
2.2k,R6,R_0402_1005Metric,C25879
1k,"R20,R21,R23",R_0402_1005Metric,C11702
TS-1187A,"SW1,SW2,SW3,SW4,SW5,SW6,SW7",SW_Push_1P1T_XKB_TS-1187A,C318884
FT2232HL,U1,LQFP-64_10x10mm_P0.5mm,C27882
93LC56B,U2,SOIC-8_3.9x4.9mm_P1.27mm,C183620
W9825G6KH-6I,U3,TSOP-II-54_22.2x10.16mm_P0.8mm,C97572
74HC165,U4,SOIC-16_3.9x9.9mm_P1.27mm,C5613
USBLC6-2SC6,U6,SOT-23-6,C7519
12MHz,Y1,Crystal_SMD_3225-4Pin_3.2x2.5mm,C9002
